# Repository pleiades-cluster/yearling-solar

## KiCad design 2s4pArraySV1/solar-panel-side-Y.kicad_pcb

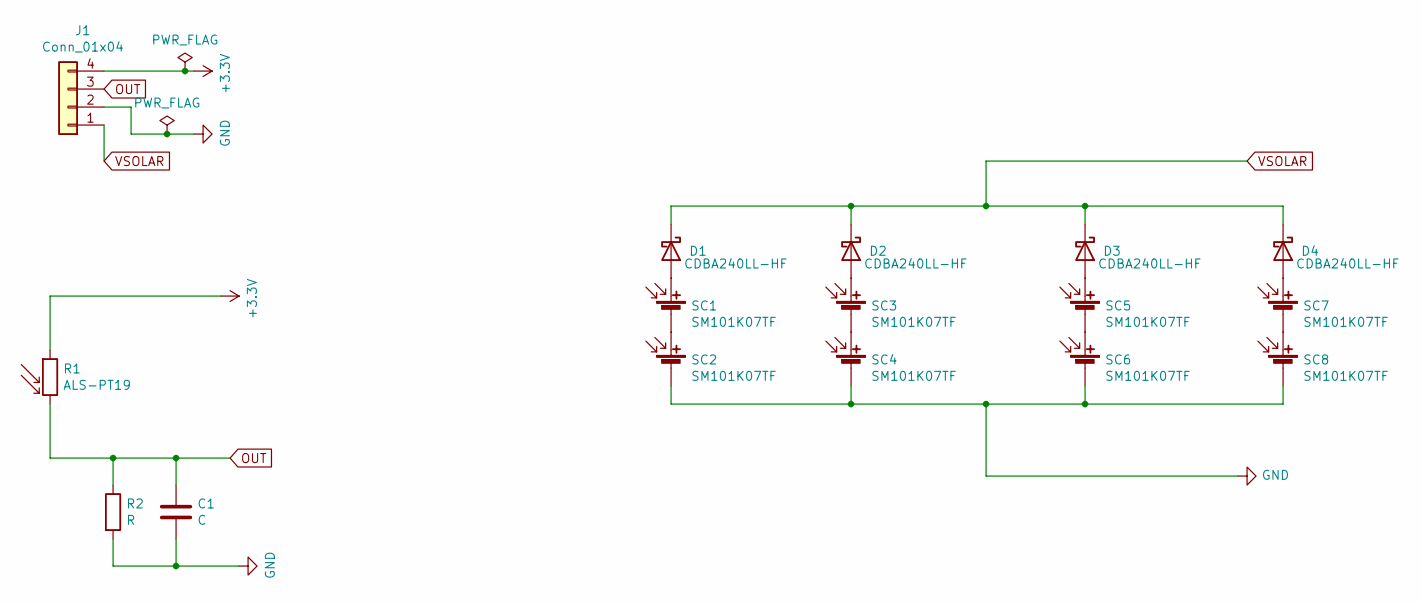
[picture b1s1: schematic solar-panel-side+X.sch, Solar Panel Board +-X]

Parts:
C1: C; C_0603_1608Metric
D1, D2, D3, D4: CDBA240LL-HF; DO-214AC
J1: Conn_01x04; PinHeader_1x04_P2.54mm_Horizontal
R1: ALS-PT19; R_0603_1608Metric
R2: R; R_0603_1608Metric
SC1, SC2, SC3, SC4, SC5, SC6, SC7, SC8: SM101K07TF

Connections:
+3V3: J1.4, R1.1
GND: C1.2, J1.2, R2.2, SC2.2 (-), SC4.2 (-), SC6.2 (-), SC8.2 (-)
unnamed: D1.2 (A), SC1.1 (+)
unnamed: D2.2 (A), SC3.1 (+)
unnamed: D3.2 (A), SC5.1 (+)
unnamed: D4.2 (A), SC7.1 (+)
unnamed: SC1.2 (-), SC2.1 (+)
unnamed: SC3.2 (-), SC4.1 (+)
unnamed: SC5.2 (-), SC6.1 (+)
unnamed: SC7.2 (-), SC8.1 (+)
OUT: C1.1, J1.3, R1.2, R2.1
VSOLAR: D1.1 (K), D2.1 (K), D3.1 (K), D4.1 (K), J1.1

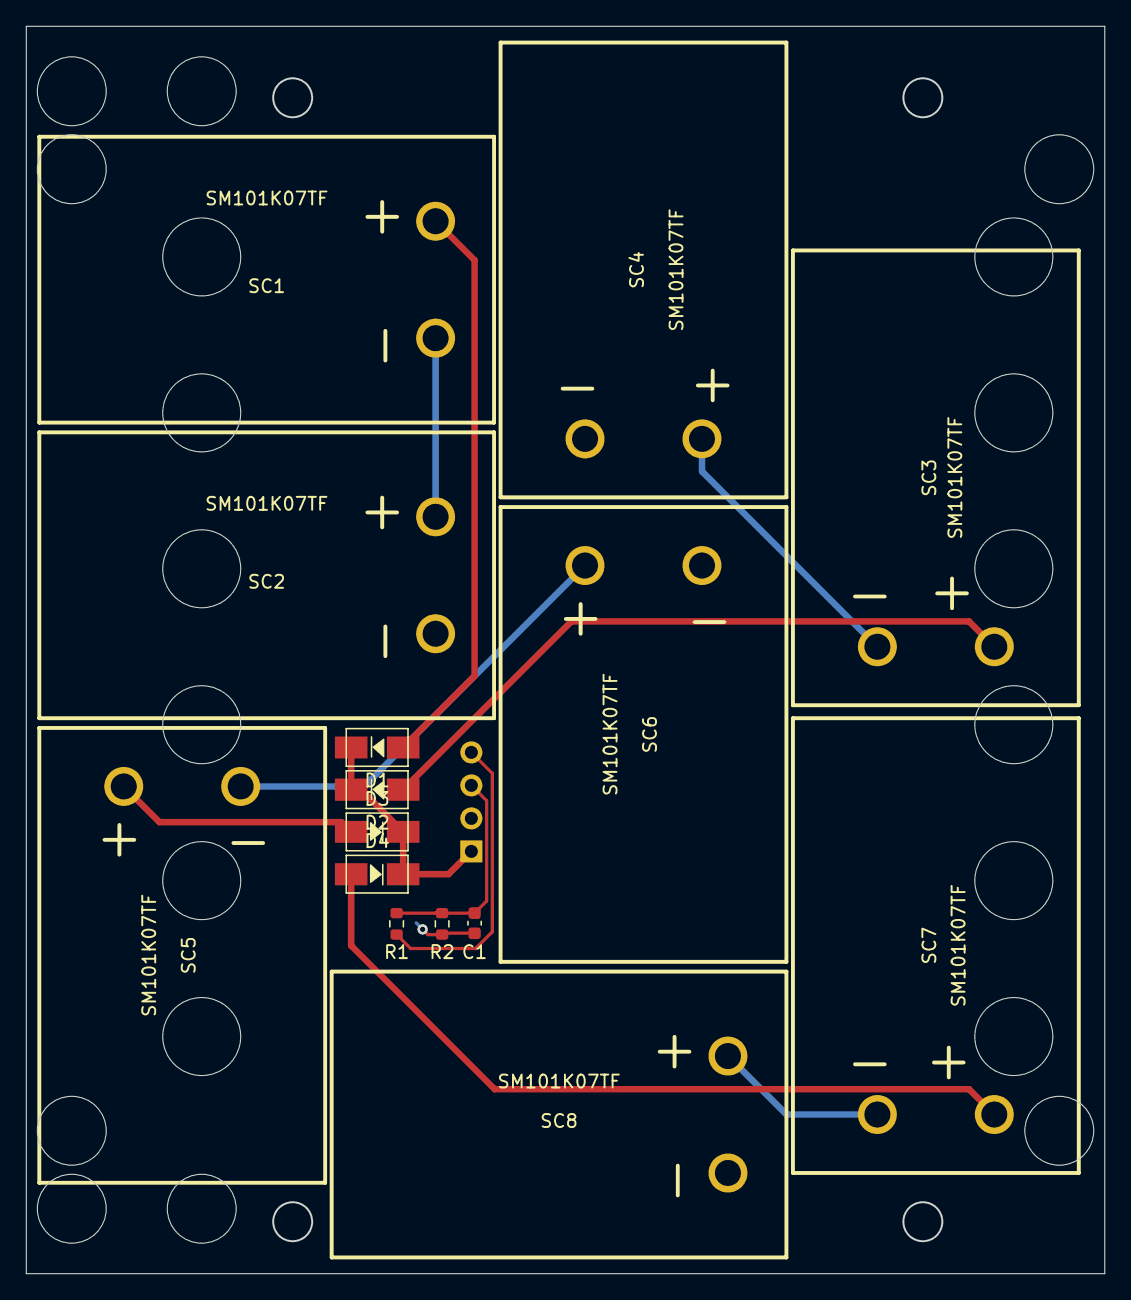
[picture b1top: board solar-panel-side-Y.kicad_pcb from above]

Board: 2 copper layers, 83.0 x 96.0 mm, 16 parts (1 on the bottom side), 12 nets.

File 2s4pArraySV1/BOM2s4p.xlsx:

|  | 2s4p Components (PER FACE):
 |  | Component | Description | Part Number | Quantity | Price (Each) | Link
 | Required for Solar Opp. | SC1 | Solar Cell | SM101K07TF | 8 | 6.39 | https://www.digikey.com/en/products/detail/anysolar-ltd/SM10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
 |  | D1-2 | schottky diode | CDBA240LL-HF | 4 | 0.56000000000000005 | https://www.digikey.com/en/products/detail/comchip-technolog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
 |  | J1 | 01x04 1.54mm connector |  | 1
 | SHOT Stuff | R1 | Light Sensor | ALS-PT19 | 1 | 0.46 | https://www.digikey.com/en/products/detail/everlight-electro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
 |  | C1 | Capacitor (50μF 1608 Metric) | GRM188R60G476ME15D | 1 | 0.56999999999999995 | https://www.digikey.com/en/products/detail/murata-electronic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
 |  | R2 | Resistor (01C 0603 1608 Metric) | CR0603-JW-103ELF | 1 | 0.1 | https://www.digikey.com/en/products/detail/bourns-inc/CR0603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
